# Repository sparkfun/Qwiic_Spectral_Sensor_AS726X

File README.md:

SparkFun Qwiic Spectral Sensor AS726X
========================================

<table class="table table-hover table-striped table-bordered">
  <tr>
   <td><a href="https://www.sparkfun.com/products/14347"><div align="center"></div></a></center></td>
   <td><a href="https://www.sparkfun.com/products/14351"><div align="center"></div></a></td>
  </tr>
  <tr>
    <td><div align="center"> <a href="https://www.sparkfun.com/products/14347">SparkFun Spectral Sensor Breakout - AS7262 Visible (Qwiic) (SEN-14347)</a></div></td>
    <td><div align="center"> <a href="https://www.sparkfun.com/products/14351">SparkFun Spectral Sensor Breakout - AS7263 NIR (Qwiic) (SEN-14351)</a></div></td>
  </tr>
</table>

This is the hardware repo for the AS726X Spectral Sensor. The AS7262 version detects wavelengths in the visible range while the AS7263 version detects wavelengths just below the visible range, in the Near Infrared (NIR) range.

Repository Contents
-------------------

* **/Enclosure** - Enclosure files
* **/Firmware** - Example code
* **/Hardware** - Eagle design files (.brd, .sch)
* **/Libraries** - Libraries for use with the AS726X
* **/Production** - Production panel files (.brd)

Documentation
--------------
* **[Library](https://github.com/sparkfun/Sparkfun_AS726X_Arduino_Library)** - Arduino library for the AS726X.
* **[Hookup Guide](https://learn.sparkfun.com/tutorials/as726x-nirvi)** - Basic hookup guide for the AS726X.

Product Versions
----------------
* [SEN-14347](https://www.sparkfun.com/products/14347)- AS7262 Visible Spectral Sensor
* [SEN-14351](https://www.sparkfun.com/products/14351)- AS7263 Near Infrared Spectral Sensor

Version History
---------------
* [V1.0.0](https://github.com/sparkfun/Qwiic_Spectral_Sensor_AS726X/tree/V1.0.0) - Initial Release

License Information
-------------------

This product is _**open source**_! 

Please review the LICENSE.md file for license information. 

If you have any questions or concerns on licensing, please contact technical support on our [SparkFun forums](https://forum.sparkfun.com/viewforum.php?f=152).

Distributed as-is; no warranty is given.

- Your friends at SparkFun.

_<COLLABORATION CREDIT>_

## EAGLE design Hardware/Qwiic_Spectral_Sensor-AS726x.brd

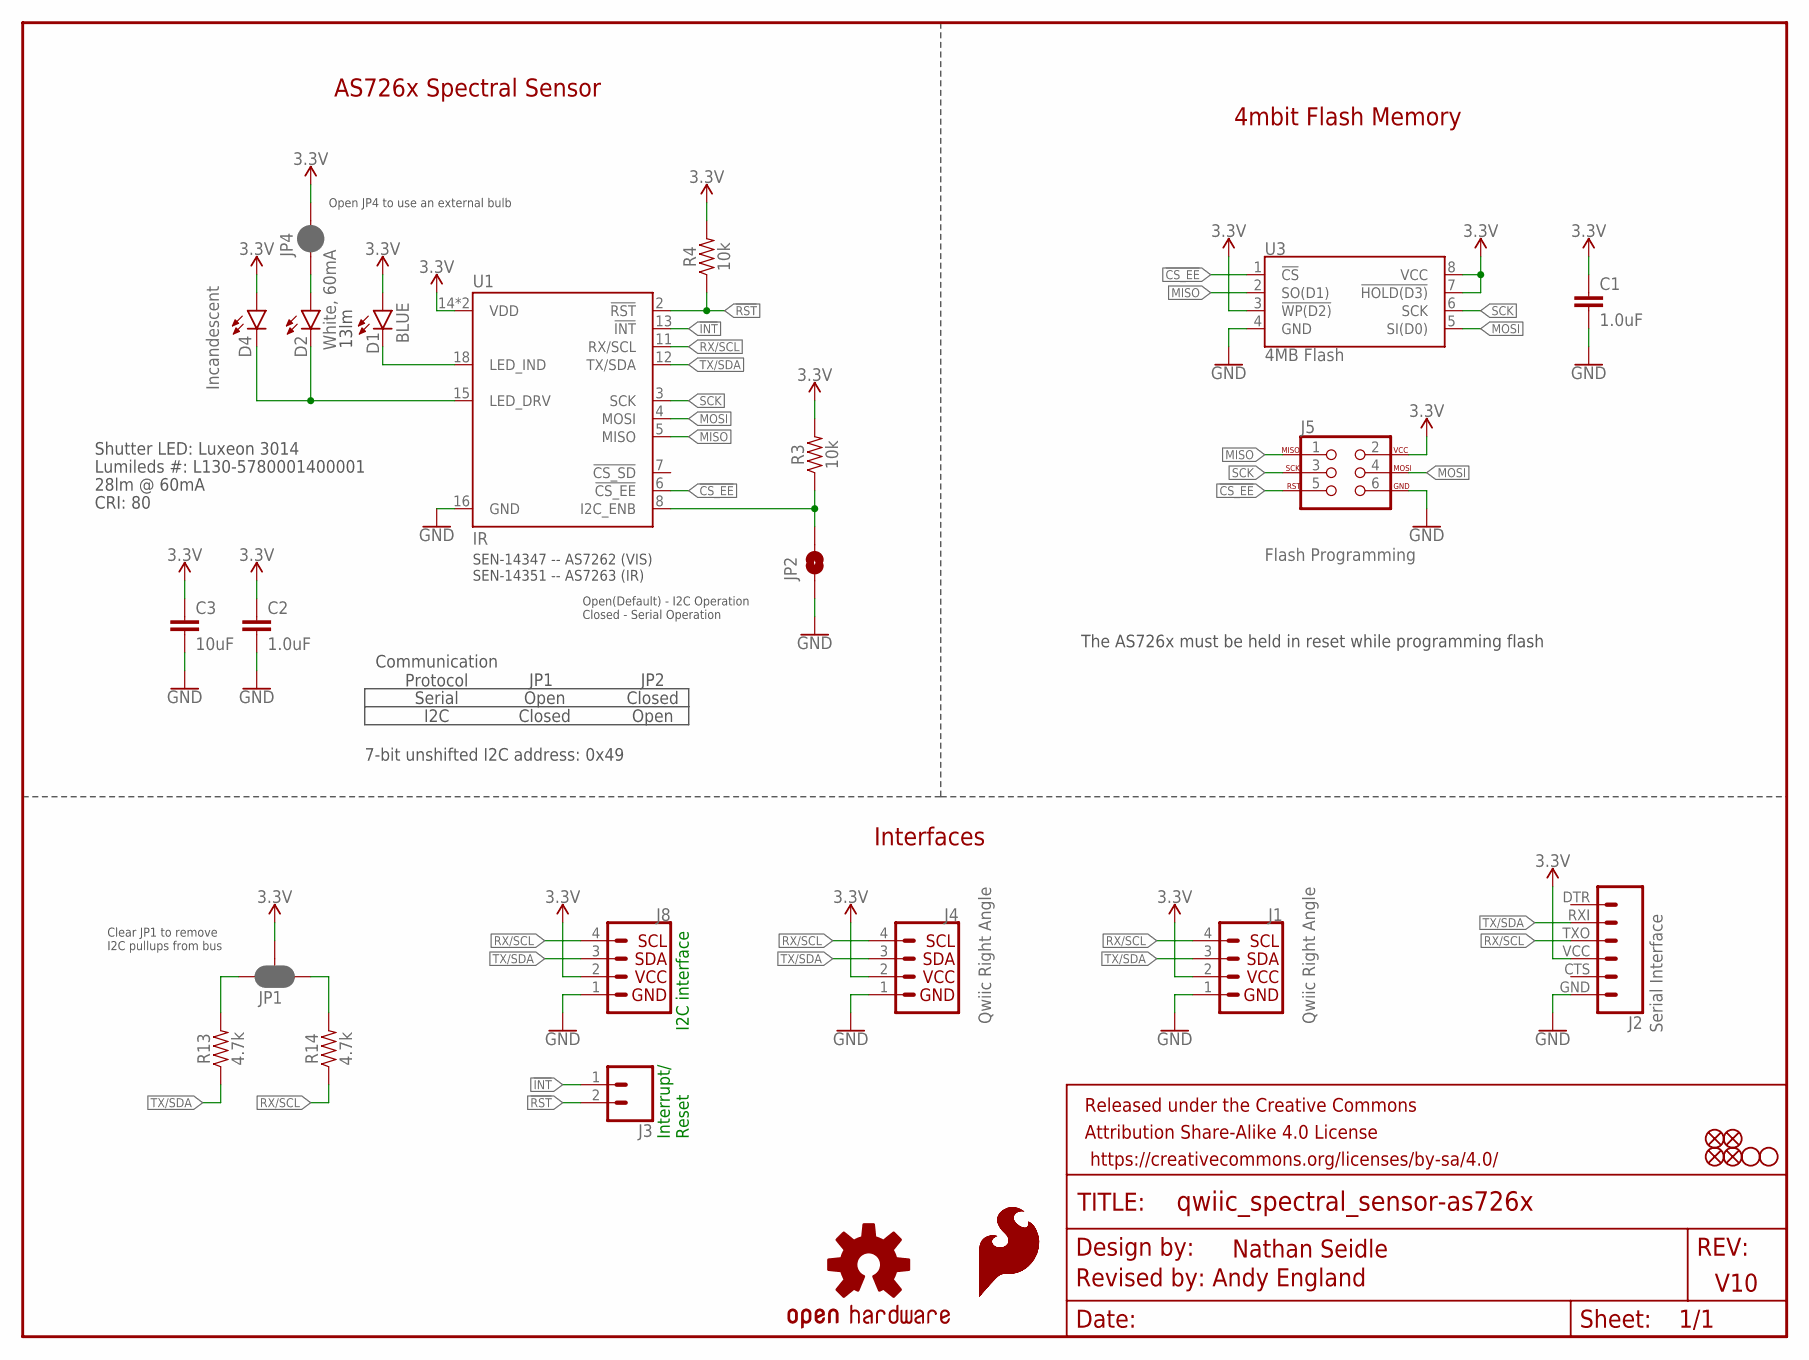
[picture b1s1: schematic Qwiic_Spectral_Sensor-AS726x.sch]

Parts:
C1, C2: 1.0uF; 0603
C3: 10uF; 0603
D1: BLUE; LED-0603
D2: White, 60mA; SUPER_BRIGHT_SMD_LED_3014
D4: Incandescent; LED_5MM_NOSILK
FD1, FD2, FD3, FD4: FIDUCIAL1X2; FIDUCIAL-1X2
FRAME1: FRAME-LETTER; CREATIVE_COMMONS
H2, H4: STAND-OFF
J1, J4: Qwiic Right Angle; 1X04_1MM_RA
J2: Serial Interface; FTDI_BASIC
J3: CONN_021X02_NO_SILK; 1X02_NO_SILK
J5: Flash Programming; 2X3_TEST_POINTS
J8: I2C_STANDARD_NO_SILK; 1X04_NO_SILK
JP1: JUMPER-SMT_3_2-NC_PASTE_SILK; SMT-JUMPER_3_2-NC_PASTE_SILK
JP2: JUMPER-SMT_2_NO_SILK; SMT-JUMPER_2_NO_SILK
JP4: JUMPER-SMT_2_NC_PASTE_NO-SILK; SMT-JUMPER_2_NC_PASTE_NO-SILK
LOGO1, LOGO2: SFE_LOGO_FLAME.2_INCH; SFE_LOGO_FLAME_.2
LOGO4: OSHW-LOGOS; OSHW-LOGO-S
R3, R4: 10k; 0603
R13, R14: 4.7k; 0603
U1: IR; LGA20
U3: 4MB Flash; SO08

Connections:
3.3V: C1.1, C2.1, C3.1, D1.A, D4.A, J1.2, J2.VCC (4), J4.2, J5.2, J8.2, JP1.2, JP4.2, R3.2, R4.2, U1.14 (VDD), U1.17 (VDD), U3.3 (!WP(D2)), U3.7 (!HOLD(D3)), U3.8 (VCC)
!CS_EE: J5.5, U1.6 (!CS_EE), U3.1 (!CS)
!INT: J3.1, U1.13 (!INT)
!RST: J3.2, R4.1, U1.2 (!RST)
GND: C1.2, C2.2, C3.2, J1.1, J2.GND (6), J4.1, J5.6, J8.1, JP2.1, U1.16 (GND), U3.4 (GND)
LED_DRV: D2.C, D4.K (C), U1.15 (LED_DRV)
MISO: J5.1, U1.5 (MISO), U3.2 (SO(D1))
MOSI: J5.4, U1.4 (MOSI), U3.5 (SI(D0))
unnamed: JP2.2, R3.1, U1.8 (I2C_ENB)
unnamed: D1.C, U1.18 (LED_IND)
unnamed: JP1.3, R13.2
unnamed: JP1.1, R14.2
unnamed: D2.A, JP4.1
RX/SCL: J1.4, J2.TXO (3), J4.4, J8.4, R14.1, U1.11 (RX/SCL)
SCK: J5.3, U1.3 (SCK), U3.6 (SCK)
TX/SDA: J1.3, J2.RXI (2), J4.3, J8.3, R13.1, U1.12 (TX/SDA)

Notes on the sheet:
AS726x Spectral Sensor
Open(Default) - I2C Operation Closed - Serial Operation
Clear JP1 to remove I2C pullups from bus
V10
Nathan Seidle
4mbit Flash Memory
Interfaces
The AS726x must be held in reset while programming flash
Open JP4 to use an external bulb
Serial
JP1
JP2
Open
Closed
Communication Protocol
I2C
13lm
Lumileds #: L130-5780001400001
Shutter LED: Luxeon 3014
28lm @ 60mA
CRI: 80
7-bit unshifted I2C address: 0x49
I2C interface
Interrupt/ Reset
Revised by: Andy England
SEN-14347 -- AS7262 (VIS) SEN-14351 -- AS7263 (IR)

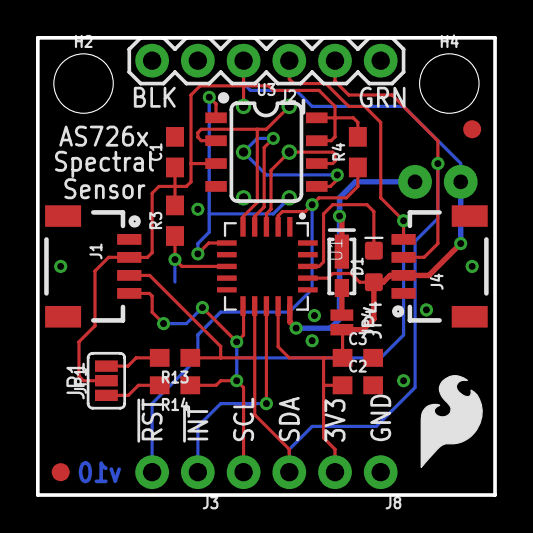
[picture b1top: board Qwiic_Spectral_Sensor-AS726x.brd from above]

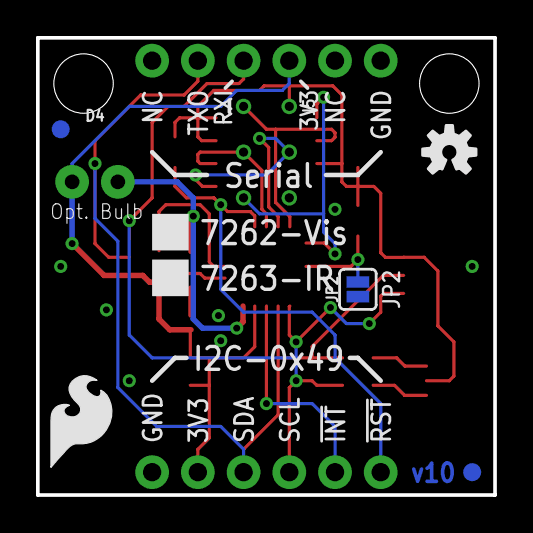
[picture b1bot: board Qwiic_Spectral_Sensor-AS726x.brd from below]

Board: 2 copper layers, 25.4 x 25.4 mm, 32 parts (7 on the bottom side), 16 nets.

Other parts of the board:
U$2: REVISION

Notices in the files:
parts and their libraries:
SparkFun-Aesthetics: Licensing: Creative Commons ShareAlike 4.0 International - https://creativecommons.org/licenses/by-sa/4.0
SparkFun-Aesthetics: Released under the Creative Commons Attribution Share-Alike 4.0 License
SparkFun-Aesthetics: https://creativecommons.org/licenses/by-sa/4.0
